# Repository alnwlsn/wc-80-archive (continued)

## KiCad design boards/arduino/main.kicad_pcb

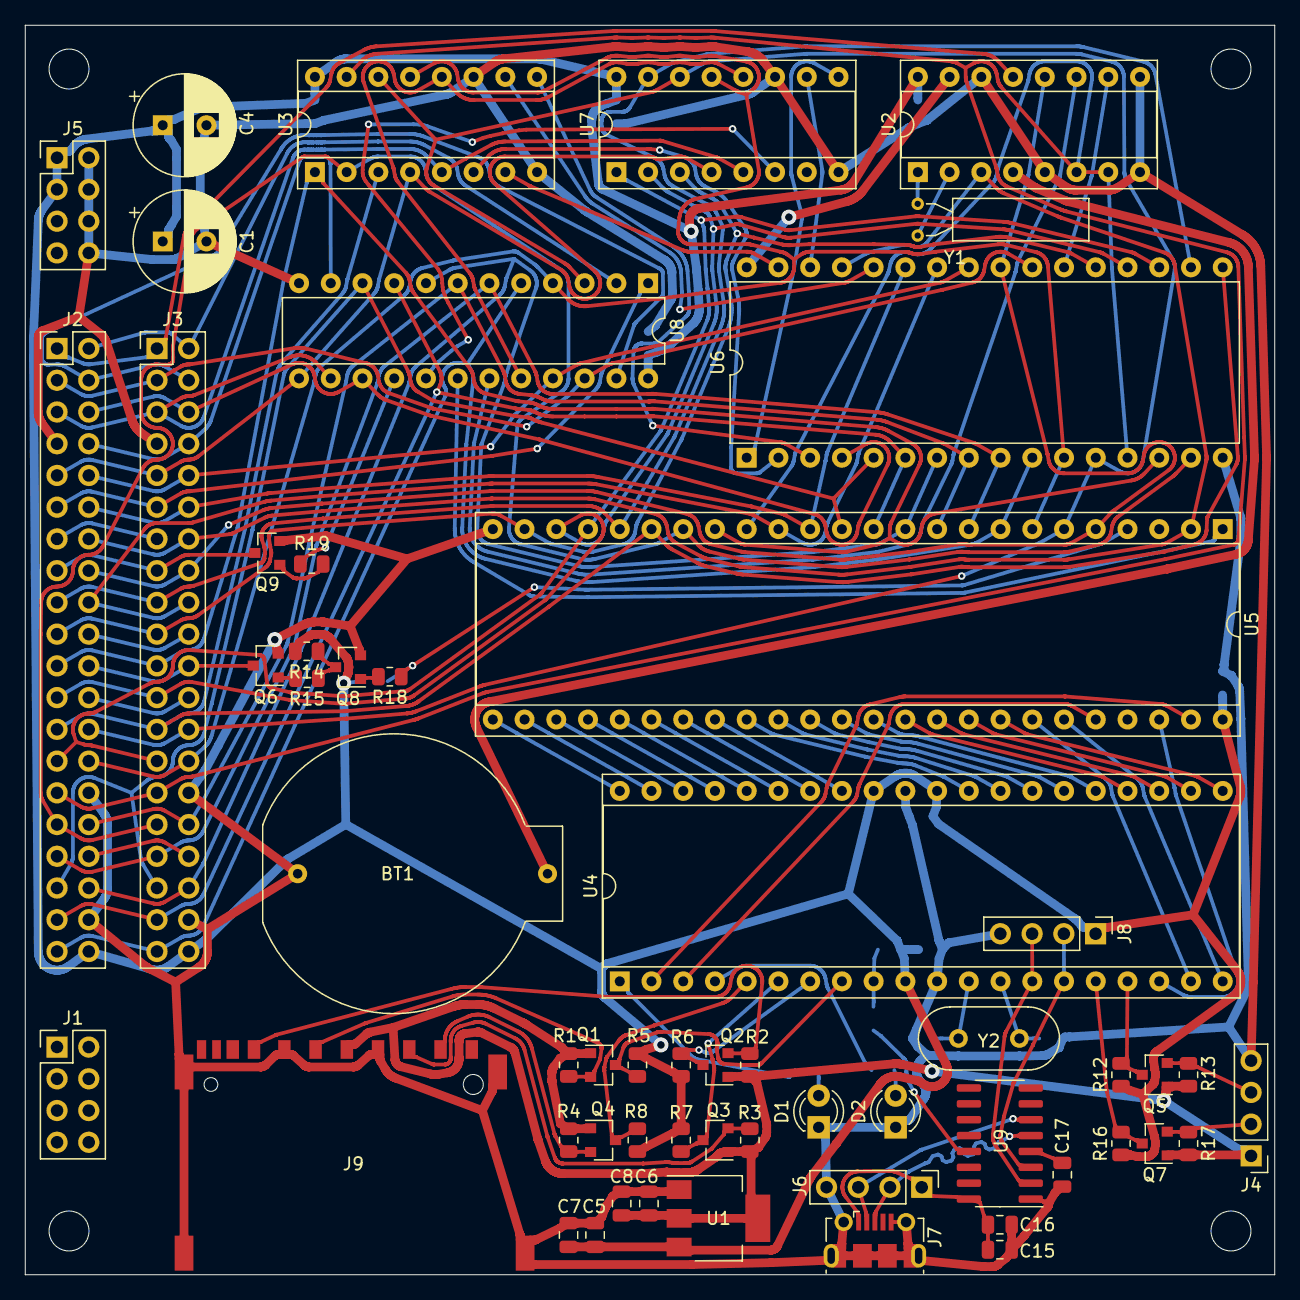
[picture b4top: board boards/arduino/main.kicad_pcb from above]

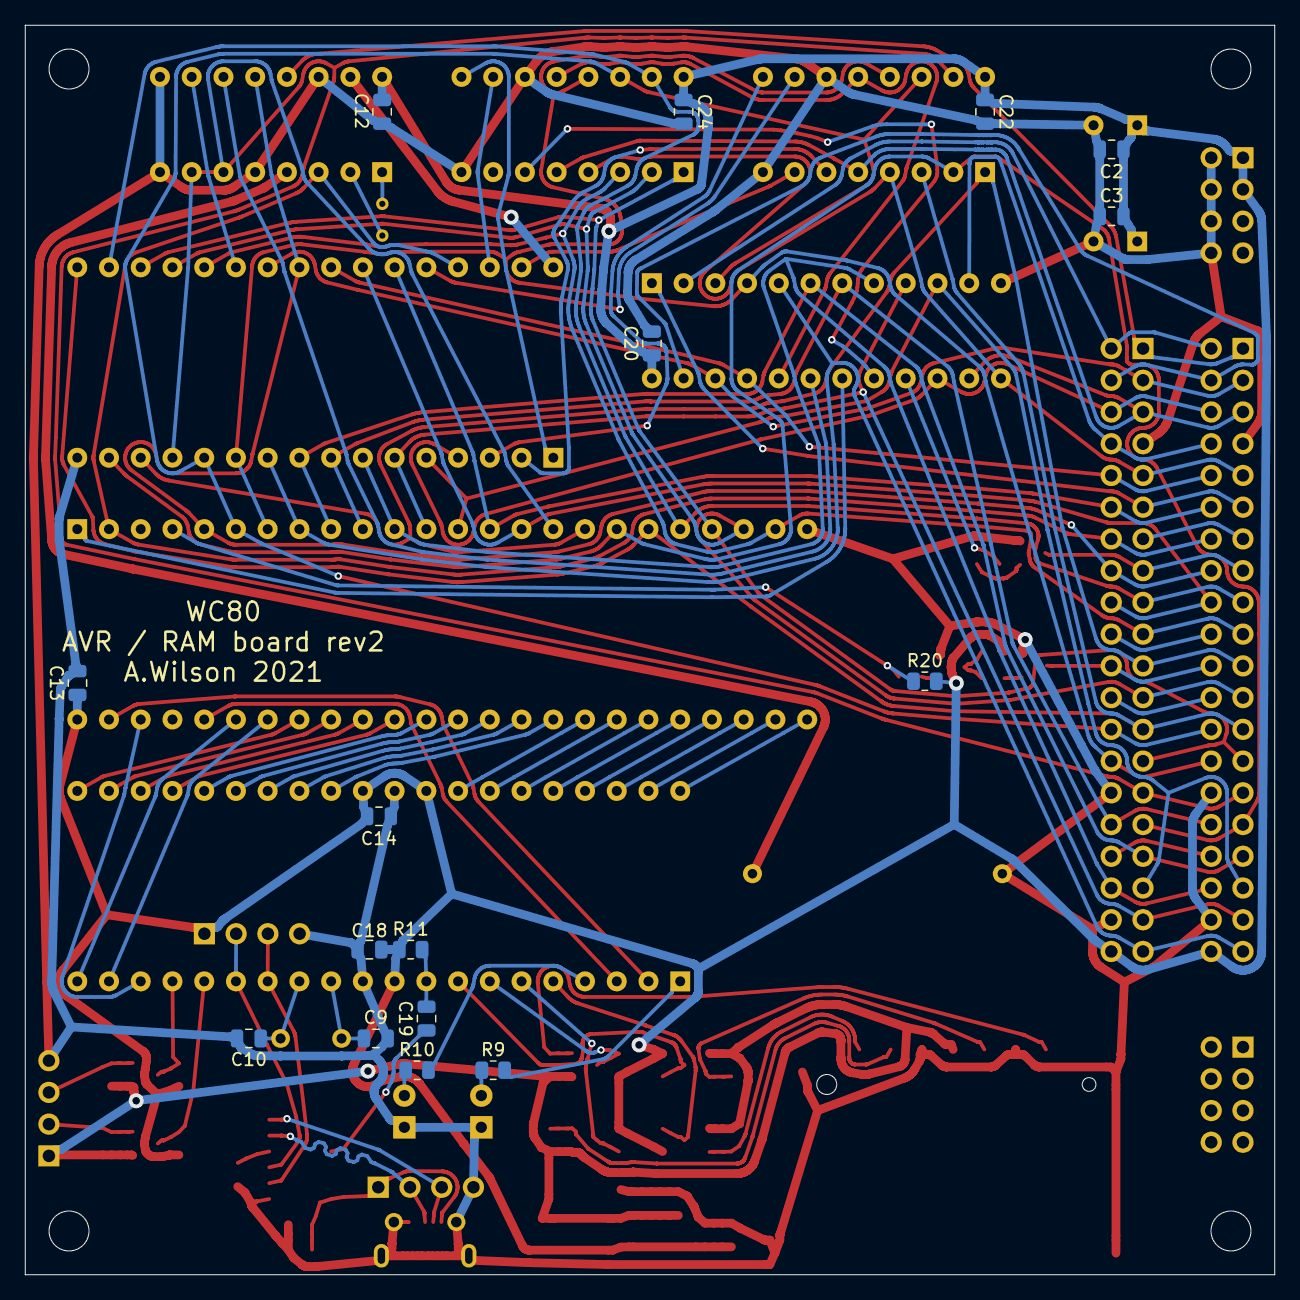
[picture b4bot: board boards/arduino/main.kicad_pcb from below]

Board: 2 copper layers, 100.0 x 100.0 mm, 77 parts (16 on the bottom side), 108 nets.

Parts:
BT1: Battery_Cell; BS-01-A4CJ004
C1, C4: 470uF; CP_Radial_D8.0mm_P3.50mm
C2, C3, C7, C8, C12, C13, C14, C18, C20, C22, C24: 100n; C_0805_2012Metric
C5, C6, C16: 10uF; C_0805_2012Metric
C9, C10: 22pF; C_0805_2012Metric
C15, C17, C19: 0.1uF; C_0805_2012Metric
D1: LED; LED_D3.0mm
D2: LED2; LED_D3.0mm
J1, J5: Conn_02x04_Odd_Even; PinHeader_2x04_P2.54mm_Vertical
J2, J3: TRS80W-header; PinHeader_2x20_P2.54mm_Vertical
J4, J6, J8: Conn_01x04_Male; PinHeader_1x04_P2.54mm_Vertical
J7: USB_B_Micro; USB_Micro-B_Molex-105017-0001
J9: SD_Card; SD_Card_ XUNPU_SD-101
M1, M2, M3, M4: 3mm-mounting-hole; MountingHole_3.2mm_M3_DIN965
Q1, Q2, Q3, Q4, Q5, Q6, Q7, Q8, Q9: BSS138; SOT-23
R1, R2, R3, R4, R5, R6, R7, R8, R11, R12, R13, R16, R17, R20: 10k; R_0805_2012Metric
R9, R10: 1000; R_0805_2012Metric
R14: 10000; R_0805_2012Metric
R15, R18, R19: 100; R_0805_2012Metric
U1: AMS1117-3.3; SOT-223-3_TabPin2
U2: DS1315; DIP-16_W7.62mm_Socket
U3, U7: 74HC670; DIP-16_W7.62mm_Socket
U4: mightycore-atmega1284p; DIP-40_W15.24mm_Socket
U5: IDT7130; DIP-48_W15.24mm_Socket
U6: AS6C4008; DIP-32_W15.24mm
U8: ATF22V10C; DIP-24_W7.62mm
U9: CH340C; SOIC-16_3.9x9.9mm_P1.27mm
Y1: 32768; Crystal_AT310_D3.0mm_L10.0mm_Horizontal
Y2: 16M; Crystal_HC49-U_Vertical

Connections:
+3V3: C6.2, C8.2, J4.1, J9.4, Q1.1, Q2.1, Q3.1, Q4.1, Q5.1, Q7.1, R1.1, R2.1, R3.1, R4.1, R13.1, R17.1, U1.2
+5V: C1.1, C2.1, C3.1, C4.1, C5.1, C7.1, C12.1, C13.1, C14.1, C18.1, C20.1, C22.1, C24.1, J2.40, J3.40, J5.1, J5.3, J8.1, R5.1, R6.1, R7.1, R8.1, R11.1, R12.1, R14.2, R16.1, R20.2, U1.3, U2.16, U3.16, U4.10, U4.30, U4.32, U5.48, U7.16, U8.24
AA0: U4.19, U5.42
AA1: U4.21, U5.41
AA2: U4.22, U5.40
AA3: U4.23, U5.39
AA4: U4.24, U5.38
AA5: U4.25, U5.37
AA6: U4.26, U5.36
AA7: U4.27, U5.35
AA8: U4.28, U5.34
AA9: U4.29, U5.33
AD0: U4.40, U5.25
AD1: U4.39, U5.26
AD2: U4.38, U5.27
AD3: U4.37, U5.28
AD4: U4.36, U5.29
AD5: U4.35, U5.30
AD6: U4.34, U5.31
AD7: U4.33, U5.32
CLK: J2.24, J3.24
F_A0: J2.26, J3.26, U3.14, U5.6, U6.12, U7.14, U8.3
F_A1: J2.28, J3.28, U3.13, U5.7, U6.11, U7.13, U8.4
F_A2: J2.39, J3.39, U5.8, U6.10, U8.5
F_A3: J2.33, J3.33, U5.9, U6.9, U8.6
F_A4: J2.32, J3.32, U5.10, U6.8, U8.7
F_A5: J2.36, J3.36, U5.11, U6.7, U8.8
F_A6: J2.37, J3.37, U5.12, U6.6, U8.9
F_A7: J2.35, J3.35, U5.13, U6.5, U8.10
F_A8: J2.12, J3.12, U5.14, U6.27
F_A9: J2.18, J3.18, U5.15, U6.26
F_A10: J2.3, J3.3, U6.23, U8.22
F_A11: J2.10, J3.10, U6.25, U8.21
F_A12: J2.6, J3.6, U6.4, U8.15
F_A13: J2.5, J3.5, U3.5, U7.5, U8.14
F_A14: J2.9, J3.9, U3.4, U7.4, U8.13
F_A15: J2.8, J3.8, U8.11
F_D0: J2.29, J3.29, U2.6, U2.7, U3.15, U5.16, U6.13
F_D1: J2.21, J3.21, U3.1, U5.17, U6.14
F_D2: J2.31, J3.31, U3.2, U5.18, U6.15
F_D3: J2.25, J3.25, U3.3, U5.19, U6.17
F_D4: J2.17, J3.17, U5.20, U6.18, U7.15
F_D5: J2.27, J3.27, U5.21, U6.19, U7.1
F_D6: J2.23, J3.23, U5.22, U6.20, U7.2
F_D7: J2.19, J3.19, U5.23, U6.21, U7.3
GND: BT1.2, C1.2, C2.2, C3.2, C4.2, C5.2, C6.1, C7.2, C8.1, C9.2, C10.2, C12.2, C13.2, C14.2, C15.2, C16.2, C17.2, C18.2, C20.2, C22.2, C24.2, D1.1, D2.1, J2.7, J2.30, J2.38, J3.7, J3.30, J3.38, J4.4, J5.2, J5.4, J5.6, J5.8, J6.4, J7.5, J7.6, J8.4, J9.3, J9.6, J9.12, J9.13, Q6.2, Q8.2, Q9.2, U1.1, U2.5, U2.8, U2.9, U2.14, U3.8, U3.11, U4.11, U4.31, U5.24, U6.16, U7.8, U7.11, U8.12, U9.1
unnamed: BT1.1, U2.4
unnamed: C9.1, U4.12, Y2.2
unnamed: C10.1, U4.13, Y2.1
unnamed: C15.1, C16.1, J6.1, J7.1, U9.16
unnamed: C17.1, U9.4
unnamed: C19.1, U9.13
unnamed: C19.2, R11.2, U4.9
unnamed: D1.2, R9.1
unnamed: D2.2, R10.1
unnamed: J4.2, Q7.2, R17.2
unnamed: J4.3, Q5.2, R13.2
unnamed: J6.2, J7.3, U9.5
unnamed: J6.3, J7.2, U9.6
unnamed: J8.2, U4.15, U9.3
unnamed: J8.3, U4.14, U9.2
unnamed: J9.1, Q4.2, R4.2
unnamed: J9.2, Q3.2, R3.2
unnamed: J9.5, Q1.2, R1.2
unnamed: J9.7, Q2.2, R2.2
unnamed: Q1.3, R5.2, U4.8
unnamed: Q2.3, R6.2, U4.7
unnamed: Q3.3, R7.2, U4.6
unnamed: Q4.3, R8.2, U4.5
unnamed: Q5.3, R12.2, U4.17
unnamed: Q6.1, R15.2
unnamed: Q7.3, R16.2, U4.16
unnamed: Q8.1, R18.2
unnamed: Q8.3, R14.1, R15.1
unnamed: Q9.1, R19.2
unnamed: R9.2, U4.1
unnamed: R10.2, U4.4
unnamed: R18.1, R20.1, U5.4
unnamed: R19.1, U8.16
unnamed: U2.1, Y1.2
unnamed: U2.2, Y1.1
unnamed: U2.10, U6.22
unnamed: U2.11, U8.19
unnamed: U2.15, U6.32
unnamed: U3.12, U7.12, U8.20
unnamed: U4.2, U5.47
unnamed: U4.3, U5.44
unnamed: U4.18, U5.46
unnamed: U4.20, U5.43
unnamed: U5.1, U8.18
S0: U3.10, U6.28
S1: U3.9, U6.3
S2: U3.7, U6.31
S3: U3.6, U6.2
S4: U6.30, U7.10
S5: U6.1, U7.9
~EN_EXTRA: U7.6, U8.17
~F_EXMEM~: J2.4, J3.4, U8.23
~F_INTAK~: J2.13, J3.13
~F_INT~: J2.22, J3.22, Q6.3
~F_INUSE~: J2.15, J3.15, Q9.3
~F_IN~: J2.20, J3.20
~F_MREQ~: J2.2, J3.2, U8.2
~F_OUT~: J2.11, J3.11, U8.1
~F_READ~: J2.16, J3.16, U2.12, U5.5, U6.24
~F_SYSRES~: J2.1, J3.1, U2.13
~F_WAIT~: J2.34, J3.34
~F_WRITE~: J2.14, J3.14, U2.3, U5.2, U6.29

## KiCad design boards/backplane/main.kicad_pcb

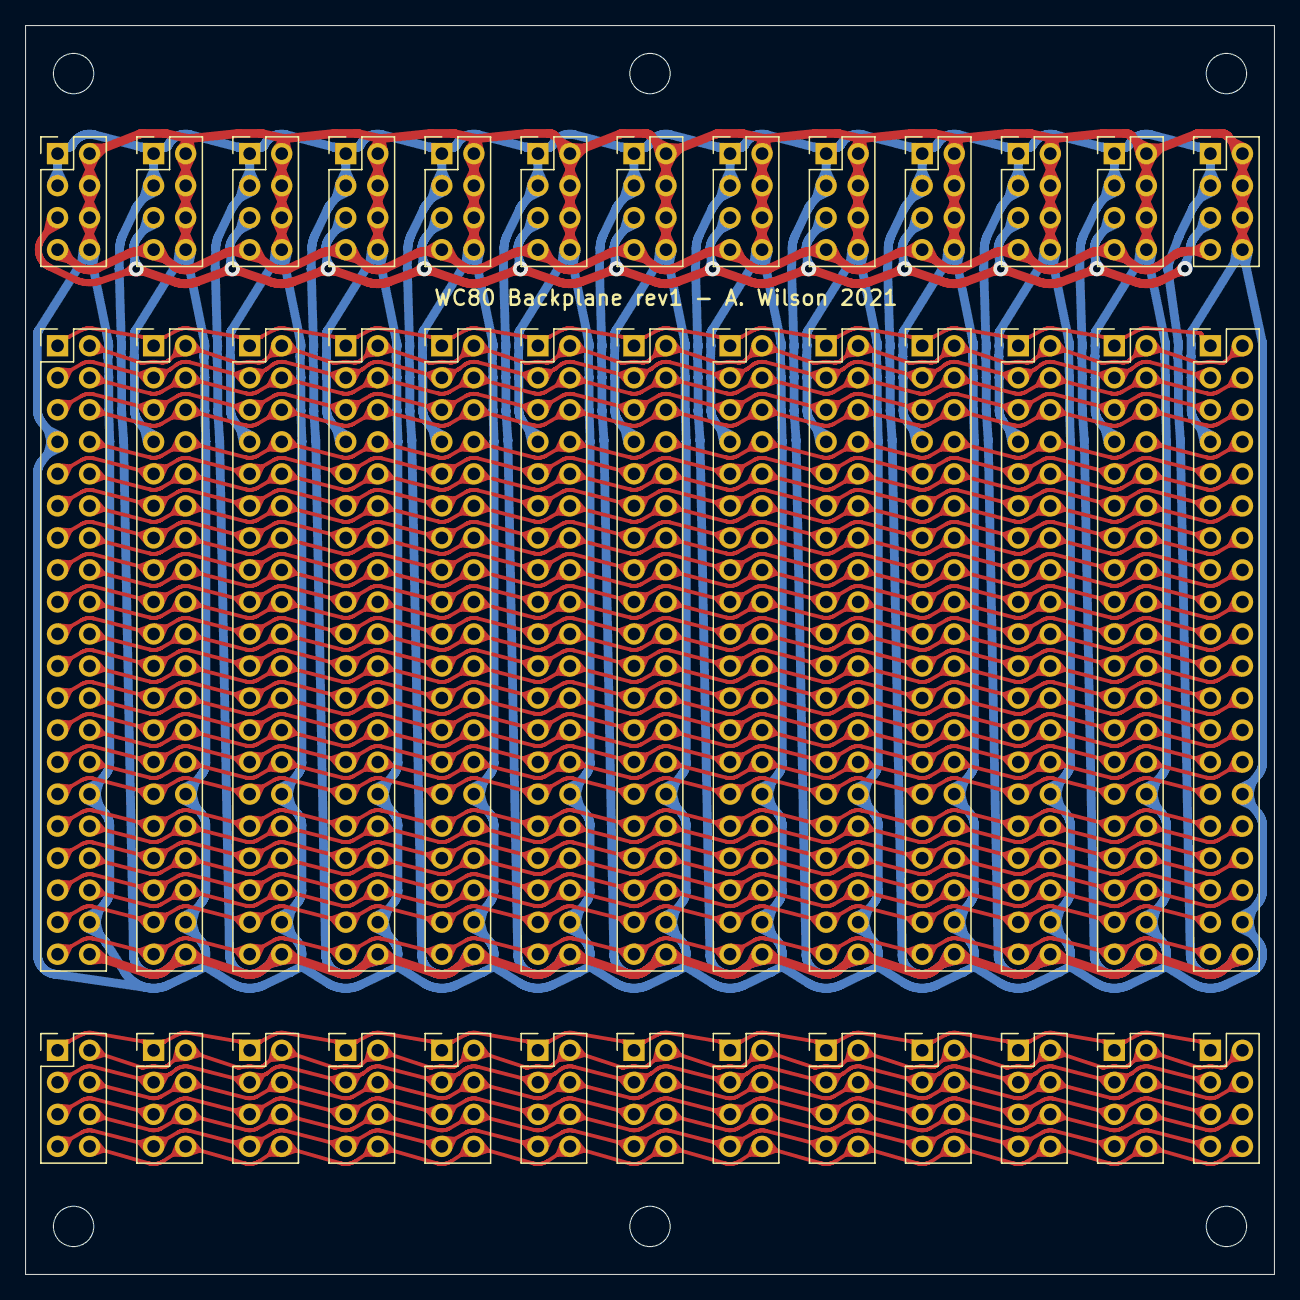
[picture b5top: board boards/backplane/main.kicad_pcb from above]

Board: 2 copper layers, 99.1 x 99.1 mm, 45 parts (0 on the bottom side), 48 nets.

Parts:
H1, H2, H3, H4, H5, H6: MountingHole; MountingHole_3.2mm_M3_DIN965
J1, J2, J4, J5, J6, J7, J8, J14, J15, J16, J17, J18, J19, J20, J21, J22, J23, J24, J31, J32, J33, J34, J35, J36, J37, J39: Conn_02x04_Odd_Even; PinHeader_2x04_P2.54mm_Vertical
J3, J9, J10, J11, J12, J13, J25, J26, J27, J28, J29, J30, J38: TRS80W-header; PinHeader_2x20_P2.54mm_Vertical

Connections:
+5V: J2.1, J2.3, J3.40, J4.1, J4.3, J5.1, J5.3, J6.1, J6.3, J7.1, J7.3, J8.1, J8.3, J9.40, J10.40, J11.40, J12.40, J13.40, J19.1, J19.3, J20.1, J20.3, J21.1, J21.3, J22.1, J22.3, J23.1, J23.3, J24.1, J24.3, J25.40, J26.40, J27.40, J28.40, J29.40, J30.40, J37.1, J37.3, J38.40
+12: J2.7, J4.7, J5.7, J6.7, J7.7, J8.7, J19.7, J20.7, J21.7, J22.7, J23.7, J24.7, J37.7
-5: J2.5, J4.5, J5.5, J6.5, J7.5, J8.5, J19.5, J20.5, J21.5, J22.5, J23.5, J24.5, J37.5
C1: J1.1, J14.1, J15.1, J16.1, J17.1, J18.1, J31.1, J32.1, J33.1, J34.1, J35.1, J36.1, J39.1
C2: J1.2, J14.2, J15.2, J16.2, J17.2, J18.2, J31.2, J32.2, J33.2, J34.2, J35.2, J36.2, J39.2
C3: J1.3, J14.3, J15.3, J16.3, J17.3, J18.3, J31.3, J32.3, J33.3, J34.3, J35.3, J36.3, J39.3
C4: J1.4, J14.4, J15.4, J16.4, J17.4, J18.4, J31.4, J32.4, J33.4, J34.4, J35.4, J36.4, J39.4
C5: J1.5, J14.5, J15.5, J16.5, J17.5, J18.5, J31.5, J32.5, J33.5, J34.5, J35.5, J36.5, J39.5
C6: J1.6, J14.6, J15.6, J16.6, J17.6, J18.6, J31.6, J32.6, J33.6, J34.6, J35.6, J36.6, J39.6
C7: J1.7, J14.7, J15.7, J16.7, J17.7, J18.7, J31.7, J32.7, J33.7, J34.7, J35.7, J36.7, J39.7
C8: J1.8, J14.8, J15.8, J16.8, J17.8, J18.8, J31.8, J32.8, J33.8, J34.8, J35.8, J36.8, J39.8
CLK: J3.24, J9.24, J10.24, J11.24, J12.24, J13.24, J25.24, J26.24, J27.24, J28.24, J29.24, J30.24, J38.24
F_A0: J3.26, J9.26, J10.26, J11.26, J12.26, J13.26, J25.26, J26.26, J27.26, J28.26, J29.26, J30.26, J38.26
F_A1: J3.28, J9.28, J10.28, J11.28, J12.28, J13.28, J25.28, J26.28, J27.28, J28.28, J29.28, J30.28, J38.28
F_A2: J3.39, J9.39, J10.39, J11.39, J12.39, J13.39, J25.39, J26.39, J27.39, J28.39, J29.39, J30.39, J38.39
F_A3: J3.33, J9.33, J10.33, J11.33, J12.33, J13.33, J25.33, J26.33, J27.33, J28.33, J29.33, J30.33, J38.33
F_A4: J3.32, J9.32, J10.32, J11.32, J12.32, J13.32, J25.32, J26.32, J27.32, J28.32, J29.32, J30.32, J38.32
F_A5: J3.36, J9.36, J10.36, J11.36, J12.36, J13.36, J25.36, J26.36, J27.36, J28.36, J29.36, J30.36, J38.36
F_A6: J3.37, J9.37, J10.37, J11.37, J12.37, J13.37, J25.37, J26.37, J27.37, J28.37, J29.37, J30.37, J38.37
F_A7: J3.35, J9.35, J10.35, J11.35, J12.35, J13.35, J25.35, J26.35, J27.35, J28.35, J29.35, J30.35, J38.35
F_A8: J3.12, J9.12, J10.12, J11.12, J12.12, J13.12, J25.12, J26.12, J27.12, J28.12, J29.12, J30.12, J38.12
F_A9: J3.18, J9.18, J10.18, J11.18, J12.18, J13.18, J25.18, J26.18, J27.18, J28.18, J29.18, J30.18, J38.18
F_A10: J3.3, J9.3, J10.3, J11.3, J12.3, J13.3, J25.3, J26.3, J27.3, J28.3, J29.3, J30.3, J38.3
F_A11: J3.10, J9.10, J10.10, J11.10, J12.10, J13.10, J25.10, J26.10, J27.10, J28.10, J29.10, J30.10, J38.10
F_A12: J3.6, J9.6, J10.6, J11.6, J12.6, J13.6, J25.6, J26.6, J27.6, J28.6, J29.6, J30.6, J38.6
F_A13: J3.5, J9.5, J10.5, J11.5, J12.5, J13.5, J25.5, J26.5, J27.5, J28.5, J29.5, J30.5, J38.5
F_A14: J3.9, J9.9, J10.9, J11.9, J12.9, J13.9, J25.9, J26.9, J27.9, J28.9, J29.9, J30.9, J38.9
F_A15: J3.8, J9.8, J10.8, J11.8, J12.8, J13.8, J25.8, J26.8, J27.8, J28.8, J29.8, J30.8, J38.8
F_D0: J3.29, J9.29, J10.29, J11.29, J12.29, J13.29, J25.29, J26.29, J27.29, J28.29, J29.29, J30.29, J38.29
F_D1: J3.21, J9.21, J10.21, J11.21, J12.21, J13.21, J25.21, J26.21, J27.21, J28.21, J29.21, J30.21, J38.21
F_D2: J3.31, J9.31, J10.31, J11.31, J12.31, J13.31, J25.31, J26.31, J27.31, J28.31, J29.31, J30.31, J38.31
F_D3: J3.25, J9.25, J10.25, J11.25, J12.25, J13.25, J25.25, J26.25, J27.25, J28.25, J29.25, J30.25, J38.25
F_D4: J3.17, J9.17, J10.17, J11.17, J12.17, J13.17, J25.17, J26.17, J27.17, J28.17, J29.17, J30.17, J38.17
F_D5: J3.27, J9.27, J10.27, J11.27, J12.27, J13.27, J25.27, J26.27, J27.27, J28.27, J29.27, J30.27, J38.27
F_D6: J3.23, J9.23, J10.23, J11.23, J12.23, J13.23, J25.23, J26.23, J27.23, J28.23, J29.23, J30.23, J38.23
F_D7: J3.19, J9.19, J10.19, J11.19, J12.19, J13.19, J25.19, J26.19, J27.19, J28.19, J29.19, J30.19, J38.19
GND: J2.2, J2.4, J2.6, J2.8, J3.7, J3.30, J3.38, J4.2, J4.4, J4.6, J4.8, J5.2, J5.4, J5.6, J5.8, J6.2, J6.4, J6.6, J6.8, J7.2, J7.4, J7.6, J7.8, J8.2, J8.4, J8.6, J8.8, J9.7, J9.30, J9.38, J10.7, J10.30, J10.38, J11.7, J11.30, J11.38, J12.7, J12.30, J12.38, J13.7, J13.30, J13.38, J19.2, J19.4, J19.6, J19.8, J20.2, J20.4, J20.6, J20.8, J21.2, J21.4, J21.6, J21.8, J22.2, J22.4, J22.6, J22.8, J23.2, J23.4, J23.6, J23.8, J24.2, J24.4, J24.6, J24.8, J25.7, J25.30, J25.38, J26.7, J26.30, J26.38, J27.7, J27.30, J27.38, J28.7, J28.30, J28.38, J29.7, J29.30, J29.38, J30.7, J30.30, J30.38, J37.2, J37.4, J37.6, J37.8, J38.7, J38.30, J38.38
~F_EXMEM~: J3.4, J9.4, J10.4, J11.4, J12.4, J13.4, J25.4, J26.4, J27.4, J28.4, J29.4, J30.4, J38.4
~F_INTAK~: J3.13, J9.13, J10.13, J11.13, J12.13, J13.13, J25.13, J26.13, J27.13, J28.13, J29.13, J30.13, J38.13
~F_INT~: J3.22, J9.22, J10.22, J11.22, J12.22, J13.22, J25.22, J26.22, J27.22, J28.22, J29.22, J30.22, J38.22
~F_INUSE~: J3.15, J9.15, J10.15, J11.15, J12.15, J13.15, J25.15, J26.15, J27.15, J28.15, J29.15, J30.15, J38.15
~F_IN~: J3.20, J9.20, J10.20, J11.20, J12.20, J13.20, J25.20, J26.20, J27.20, J28.20, J29.20, J30.20, J38.20
~F_MREQ~: J3.2, J9.2, J10.2, J11.2, J12.2, J13.2, J25.2, J26.2, J27.2, J28.2, J29.2, J30.2, J38.2
~F_OUT~: J3.11, J9.11, J10.11, J11.11, J12.11, J13.11, J25.11, J26.11, J27.11, J28.11, J29.11, J30.11, J38.11
~F_READ~: J3.16, J9.16, J10.16, J11.16, J12.16, J13.16, J25.16, J26.16, J27.16, J28.16, J29.16, J30.16, J38.16
~F_SYSRES~: J3.1, J9.1, J10.1, J11.1, J12.1, J13.1, J25.1, J26.1, J27.1, J28.1, J29.1, J30.1, J38.1
~F_WAIT~: J3.34, J9.34, J10.34, J11.34, J12.34, J13.34, J25.34, J26.34, J27.34, J28.34, J29.34, J30.34, J38.34
~F_WRITE~: J3.14, J9.14, J10.14, J11.14, J12.14, J13.14, J25.14, J26.14, J27.14, J28.14, J29.14, J30.14, J38.14

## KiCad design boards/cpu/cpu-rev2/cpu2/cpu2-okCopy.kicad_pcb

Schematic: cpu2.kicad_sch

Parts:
BT1: Battery_Cell; BS-01-A4CJ004
C1: 4u7; C_0805_2012Metric
C2: 2u2; C_0805_2012Metric
C3, C4, C5, C6, C7, C8, C9, C10, C11, C12, C13, C14, C15, C16, C18, C19, C20, C27, C28, C29: 100n; C_0805_2012Metric
C17, C21: 470uF; CP_Radial_D8.0mm_P3.50mm
C22: 100uF; CP_Elec_5x5.4
C23, C24: 220pF; C_0805_2012Metric
C25, C26: 10uF; C_0805_2012Metric
D3: HALT; LED_D3.0mm_FlatTop
D5: PWR; LED_D3.0mm_FlatTop
D8: 32; LED_D3.0mm_FlatTop
D9, D10, D11, D12, D13: 1N4148; D_SOD-123
J1, J2: Conn_02x04_Odd_Even; PinHeader_2x04_P2.54mm_Vertical
J3: TRS80W-header; PinHeader_2x20_P2.54mm_Vertical
J4: Conn_01x06_Male; PinHeader_1x06_P2.54mm_Vertical
M1, M2, M3, M4: 3mm-mounting-hole; MountingHole_3.2mm_M3_DIN965
Q1: 2N3904; TO-92_Inline
R3, R4, R52: 10; R_0805_2012Metric
R5, R6, R7, R9, R10, R15, R16, R17, R18, R19, R20, R21, R22, R23, R24, R25, R26, R27, R28, R29, R30, R31, R32, R33, R34, R35, R36, R37, R38, R39, R40, R41, R42, R43, R44, R45: 4k7; R_0805_2012Metric
R8, R11, R46, R48: 1K; R_0805_2012Metric
R47, R49: 7k5; R_0805_2012Metric
R50: 220K; R_0805_2012Metric
R51: 1.2K; R_0805_2012Metric
R53: 100; R_0805_2012Metric
R54, R61, R63, R65, R66: 470K; R_0805_2012Metric
R55, R59: 360K; R_0805_2012Metric
R56, R57: 1M; R_0805_2012Metric
R58: 560K; R_0805_2012Metric
R60: 1.8M; R_0805_2012Metric
R62: 680K; R_0805_2012Metric
R64: 10K; R_0805_2012Metric
SW1: NMI; SW_PUSH_6mm
SW2: RESET; SW_PUSH_6mm
U1, U20: 74LS175; SOIC-16_3.9x9.9mm_P1.27mm
U2: 74LS132; SOIC-14_3.9x8.7mm_P1.27mm
U3: 74LS163; SOIC-16_3.9x9.9mm_P1.27mm
U4: 74LS74; SOIC-14_3.9x8.7mm_P1.27mm
U5: Z80CPU; DIP-40_W15.24mm_Socket
U6: 74LS32; SOIC-14_3.9x8.7mm_P1.27mm
U8: SST39SF040; DIP-32_W15.24mm_Socket
U9: ATF22V10C; DIP-24_W7.62mm_Socket
U10: 74HC245; SO-20_5.3x12.6mm_P1.27mm
U11: AS6C4008; DIP-32_W15.24mm_Socket
U12, U15, U16: 74HC244; SO-20_5.3x12.6mm_P1.27mm
U13, U14: 74HC670; SOIC-16_3.9x9.9mm_P1.27mm
U17: LM3900D; SOIC-14_3.9x8.7mm_P1.27mm
U18: 74HCT02; SOIC-14_3.9x8.7mm_P1.27mm
U19: 74LS125; SOIC-14_3.9x8.7mm_P1.27mm
U21: SIP-1A05
U22: DS1210; SOIC-8_3.9x4.9mm_P1.27mm
X1: SG-7050CAN; Oscillator_SMD_SeikoEpson_SG8002CA-4Pin_7.0x5.0mm

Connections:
+5V: C1.1, C2.1, C3.1, C4.1, C5.1, C6.1, C7.1, C8.1, C9.1, C10.1, C11.1, C12.1, C13.1, C14.1, C15.1, C16.1, C17.1, C18.1, C19.1, C20.1, C21.1, C27.1, C28.1, C29.1, D3.2 (A), D5.2 (A), D9.1 (K), J2.1, J2.3, J3.40 (+5V), R7.2, R9.2, R10.2, R16.2, R17.2, R18.2, R19.2, R20.2, R45.2, R50.1, R52.1, R64.1, SW1.1 (A), SW2.1 (A), U1.16 (VCC), U2.14 (VCC), U3.16 (VCC), U4.14 (VCC), U5.11 (VCC), U6.14 (VCC), U8.31 (~WE), U8.32 (VCC), U9.24 (VCC), U10.20 (VCC), U12.20 (VCC), U13.16 (VCC), U14.16 (VCC), U15.20 (VCC), U16.20 (VCC), U18.14 (VCC), U19.14 (VCC), U20.16 (VCC), U21.3 (COIL2), U22.8 (VCCI), X1.1 (~ST), X1.4 (VCC)
A0: U5.30 (A0), U8.12 (A0), U9.10, U11.12 (A0), U12.2 (1A0), U13.14 (Wa), U14.14 (Wa)
A1: U5.31 (A1), U8.11 (A1), U9.9, U11.11 (A1), U12.4 (1A1), U13.13 (Wb), U14.13 (Wb)
A2: U5.32 (A2), U8.10 (A2), U9.8, U11.10 (A2), U12.6 (1A2)
A3: U5.33 (A3), U8.9 (A3), U9.7, U11.9 (A3), U12.8 (1A3)
A4: U5.34 (A4), U8.8 (A4), U9.6, U11.8 (A4), U12.17 (2A0)
A5: U5.35 (A5), U8.7 (A5), U9.5, U11.7 (A5), U12.15 (2A1)
A6: U5.36 (A6), U8.6 (A6), U9.4, U11.6 (A6), U12.13 (2A2)
A7: U5.37 (A7), U8.5 (A7), U9.3, U11.5 (A7), U12.11 (2A3)
A8: U5.38 (A8), U8.27 (A8), U11.27 (A8), U15.2 (1A0)
A9: U5.39 (A9), U8.26 (A9), U11.26 (A9), U15.4 (1A1)
A10: U5.40 (A10), U8.23 (A10), U11.23 (A10), U15.6 (1A2)
A11: U5.1 (A11), U8.25 (A11), U11.25 (A11), U15.8 (1A3)
A12: U5.2 (A12), U8.4 (A12), U11.4 (A12), U15.17 (2A0)
A13: U5.3 (A13), U8.28 (A13), U11.28 (A13), U15.15 (2A1)
A14: U5.4 (A14), U13.5 (Ra), U14.5 (Ra), U15.13 (2A2)
A15: U5.5 (A15), U13.4 (Rb), U14.4 (Rb), U15.11 (2A3)
BB_CE: U11.22 (~CE), U22.6 (~CEO)
BB_VCC: U11.32 (VCC), U22.1 (VCCO)
BUSISO: J1.7, R15.2, U10.19 (CE), U12.1 (1OE), U12.19 (2OE), U15.1 (1OE), U15.19 (2OE), U16.1 (1OE), U16.19 (2OE)
C1INN: R58.2, U17.6 (1IN-)
C1INP: R59.1, R60.2, U17.1 (1IN+)
C1OUT: D13.2 (A), R55.2, R58.1, R61.1, U17.5 (1OUT)
C2INN: R61.2, R63.1, U17.3 (2IN-)
C2INP: R62.1, U17.2 (2IN+)
C2OUT: D10.2 (A), R63.2, U17.4 (2OUT)
C3INN: R54.2, R56.1, U17.8 (3IN-)
C3INP: R57.2, U17.13 (3IN+)
C3OUT: D11.2 (A), R56.2, R66.2, U17.9 (3OUT)
C4INN: R65.1, U17.11 (4IN-)
C4INP: R66.1, U17.12 (4IN+)
CASIND: U2.1, U17.10 (4OUT)
CASSAIN: C23.2, J4.1, R53.1
CASSAOUT: J4.3, R47.2, R49.1, R51.2
CASSIN: U9.20, U19.1
CASSOUT: U2.5, U9.19, U20.9 (Cp)
CASS_SW1: J4.6, U21.1 (SW1)
CASS_SW2: J4.5, U21.4 (SW2)
CLK: J3.24 (CLK), U4.5 (Q), U5.6 (~CLK)
CLKD0: U1.2 (Q0), U3.3 (D0)
CLKD1: U1.7 (Q1), U3.4 (D1)
CLKD2: U1.10 (Q2), U3.5 (D2)
CLKDIV: U1.9 (Cp), U9.21
D0: R29.1, U1.4 (D0), U5.14 (D0), U8.13 (D0), U10.2 (A0), U11.13 (D0), U13.15 (D1), U20.4 (D0)
D1: R30.1, U1.5 (D1), U5.15 (D1), U8.14 (D1), U10.3 (A1), U11.14 (D1), U13.1 (D2), U20.5 (D1)
D2: R31.1, U1.12 (D2), U5.12 (D2), U8.15 (D2), U10.4 (A2), U11.15 (D2), U13.2 (D3), U20.12 (D2)
D3: R32.1, U1.13 (D3), U5.8 (D3), U8.17 (D3), U10.5 (A3), U11.17 (D3), U13.3 (D4), U20.13 (D3)
D4: R33.1, U5.7 (D4), U8.18 (D4), U10.6 (A4), U11.18 (D4), U14.15 (D1)
D5: R34.1, U5.9 (D5), U8.19 (D5), U10.7 (A5), U11.19 (D5), U14.1 (D2)
D6: R35.1, U5.10 (D6), U8.20 (D6), U10.8 (A6), U11.20 (D6), U14.2 (D3)
D7: R36.1, U5.13 (D7), U8.21 (D7), U10.9 (A7), U11.21 (D7), U14.3 (D4), U19.3
F_A0: J3.26 (A0), U12.18 (1Y0)
F_A1: J3.28 (A1), U12.16 (1Y1)
F_A2: J3.39 (A2), U12.14 (1Y2)
F_A3: J3.33 (A3), U12.12 (1Y3)
F_A4: J3.32 (A4), U12.3 (2Y0)
F_A5: J3.36 (A5), U12.5 (2Y1)
F_A6: J3.37 (A6), U12.7 (2Y2)
F_A7: J3.35 (A7), U12.9 (2Y3)
F_A8: J3.12 (A8), U15.18 (1Y0)
F_A9: J3.18 (A9), U15.16 (1Y1)
F_A10: J3.3 (A10), U15.14 (1Y2)
F_A11: J3.10 (A11), U15.12 (1Y3)
F_A12: J3.6 (A12), U15.3 (2Y0)
F_A13: J3.5 (A13), U15.5 (2Y1)
F_A14: J3.9 (A14), U15.7 (2Y2)
F_A15: J3.8 (A15), U15.9 (2Y3)
F_D0: J3.29 (D0), R37.1, U10.18 (B0)
F_D1: J3.21 (D1), R38.1, U10.17 (B1)
F_D2: J3.31 (D2), R39.1, U10.16 (B2)
F_D3: J3.25 (D3), R40.1, U10.15 (B3)
F_D4: J3.17 (D4), R41.1, U10.14 (B4)
F_D5: J3.27 (D5), R42.1, U10.13 (B5)
F_D6: J3.23 (D6), R43.1, U10.12 (B6)
F_D7: J3.19 (D7), R44.1, U10.11 (B7)
GND: BT1.2 (-), C3.2, C4.2, C5.2, C6.2, C7.2, C8.2, C9.2, C10.2, C11.2, C12.2, C13.2, C14.2, C15.2, C16.2, C17.2, C18.2, C19.2, C20.2, C21.2, C22.2, C25.2, C26.2, C27.2, C28.2, C29.2, D8.1 (K), J2.2, J2.4, J2.6, J2.8, J3.7 (GND), J3.30 (GND), J3.38 (GND), J4.2, J4.4, Q1.1 (E), R5.2, R6.2, R11.1, R15.1, R21.2, R22.2, R23.2, R24.2, R25.2, R26.2, R27.2, R28.2, R29.2, R30.2, R31.2, R32.2, R33.2, R34.2, R35.2, R36.2, R37.2, R38.2, R39.2, R40.2, R41.2, R42.2, R43.2, R44.2, R51.1, R53.2, U1.8 (GND), U2.7 (GND), U3.6 (D3), U3.8 (GND), U4.7 (GND), U4.11 (C), U4.12 (D), U5.29 (GND), U6.7 (GND), U8.16 (GND), U9.12 (GND), U10.10 (GND), U11.16 (GND), U12.10 (GND), U13.8 (GND), U14.8 (GND), U15.10 (GND), U16.10 (GND), U17.7 (GND), U18.7 (GND), U18.8, U18.9, U19.4, U19.7 (GND), U19.10, U19.13, U20.8 (GND), U22.3 (TOL), U22.4 (GND), U22.7 (VBAT2), X1.2 (GND)
M1: U5.27 (~M1), U18.5
MEMCHIP: R26.1, U9.14, U14.9 (Q2)
unnamed: BT1.1 (+), U22.2 (VBAT1)
unnamed: C1.2, R3.1, R5.1, U2.9, U2.10
unnamed: C2.2, R4.1, R6.1, U2.12, U2.13
unnamed: C22.1, R52.2, U17.14 (VCC)
unnamed: C23.1, C24.1, R55.1
unnamed: C24.2, R59.2
unnamed: C25.1, R57.1, R60.1, R62.2, R64.2
unnamed: C26.1, D12.1 (K), R65.2
unnamed: D3.1 (K), R8.2
unnamed: D5.1 (K), R11.2
unnamed: D8.2 (A), R46.1
unnamed: D9.2 (A), Q1.3 (C), U21.2 (COIL1)
unnamed: D10.1 (K), D13.1 (K), R54.1
unnamed: D11.1 (K), D12.2 (A)
unnamed: J1.1, R4.2, SW2.2 (B)
unnamed: J1.3, R3.2, SW1.2 (B)
unnamed: J1.5, U2.8, U5.17 (~NMI)
unnamed: Q1.2 (B), R48.1
unnamed: R7.1, U3.1 (~MR), U3.7 (CEP), U3.10 (CET)
unnamed: R8.1, U5.18 (~HALT)
unnamed: R9.1, U5.25 (~BUSRQ)
unnamed: R10.1, U4.1 (~R), U4.4 (~S)
unnamed: R45.1, U20.1 (~Mr)
unnamed: R46.2, U20.15 (Q3)
unnamed: R47.1, U20.2 (Q0)
unnamed: R48.2, U20.10 (Q2)
unnamed: R49.2, R50.2, U20.6 (~Q1)
unnamed: U2.2, U2.6
unnamed: U3.2 (CP), X1.3 (OUT)
unnamed: U4.2 (D), U4.6 (~Q)
unnamed: U4.8 (~Q), U13.11 (~RD), U14.11 (~RD)
unnamed: U3.9 (~PE), U18.1
unnamed: U3.11 (Q3), U4.3 (C), U18.2, U18.3
unnamed: U18.4, U18.11, U18.12
unnamed: U2.3, U2.4, U19.2
RAM~ROM~: R27.1, U9.15
S0: R21.1, U8.29 (A14), U11.3 (A14), U13.10 (Q1)
S1: R22.1, U8.3 (A15), U11.31 (A15), U13.9 (Q2)
S2: R23.1, U8.2 (A16), U11.2 (A16), U13.7 (Q3)
S3: R24.1, U8.30 (A17), U11.30 (A17), U13.6 (Q4)
S4: R25.1, U8.1 (A18), U11.1 (A18), U14.10 (Q1)
~BUSBUF~: U9.22, U10.1 (A->B)
~BankSel~: U4.10 (~S), U9.16, U13.12 (~WR), U14.12 (~WR)
~EXMEM~: R28.1, U14.6 (Q4), U16.6 (1A2)
~F_EXMEM~: J3.4 (~EXMEM), U16.14 (1Y2)
~F_INTAK~: J3.13 (~INTAK), U16.12 (1Y3)
~F_INT~: J3.22 (~INT), R19.1, U19.5
~F_INUSE~: J3.15 (~INUSE), R18.1, U19.9
~F_IN~: J3.20 (~IN), U16.5 (2Y1)
~F_MREQ~: J3.2 (~RAS), U16.16 (1Y1)
~F_OUT~: J3.11 (~OUT), U16.3 (2Y0)
~F_READ~: J3.16 (~RD), U16.9 (2Y3)
~F_SYSRES~: J3.1 (~SYSRES), U16.18 (1Y0)
~F_WAIT~: J3.34 (~WAIT), R20.1, U19.12
~F_WRITE~: J3.14 (~WR), U16.7 (2Y2)
~INTAK~: U16.8 (1A3), U18.13
~INT~: R16.1, U5.16 (~INT), U19.6
~INUSE~: U9.13, U19.8
~IN~: U6.8, U16.15 (2A1)
~IORQ~: U5.20 (~IORQ), U6.10, U6.13, U9.23, U18.6
~MREQ~: U5.19 (~MREQ), U6.2, U6.5, U9.2, U16.4 (1A1)
~OUT~: U6.11, U9.1, U16.17 (2A0)
~RAM0~: U9.18, U22.5 (~CE)
~RD~: U5.21 (~RD), U6.1, U6.9, U9.11
~READ~: U6.3, U8.24 (~OE), U11.24 (~OE), U16.11 (2A3)
~ROM0~: U8.22 (~CE), U9.17
~SYSRES~: U1.1 (~Mr), U2.11, U4.13 (~R), U5.26 (~RESET), U16.2 (1A0)
~WAIT~: R17.1, U5.24 (~WAIT), U19.11
~WRITE~: U6.6, U11.29 (~WE), U16.13 (2A2)
~WR~: U5.22 (~WR), U6.4, U6.12

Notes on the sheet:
WC-80 CPU rev2 - Alan Wilson 2022
rev3 - ~OUT~ can be changed to ~WR~, because ~OUT~ can be derived

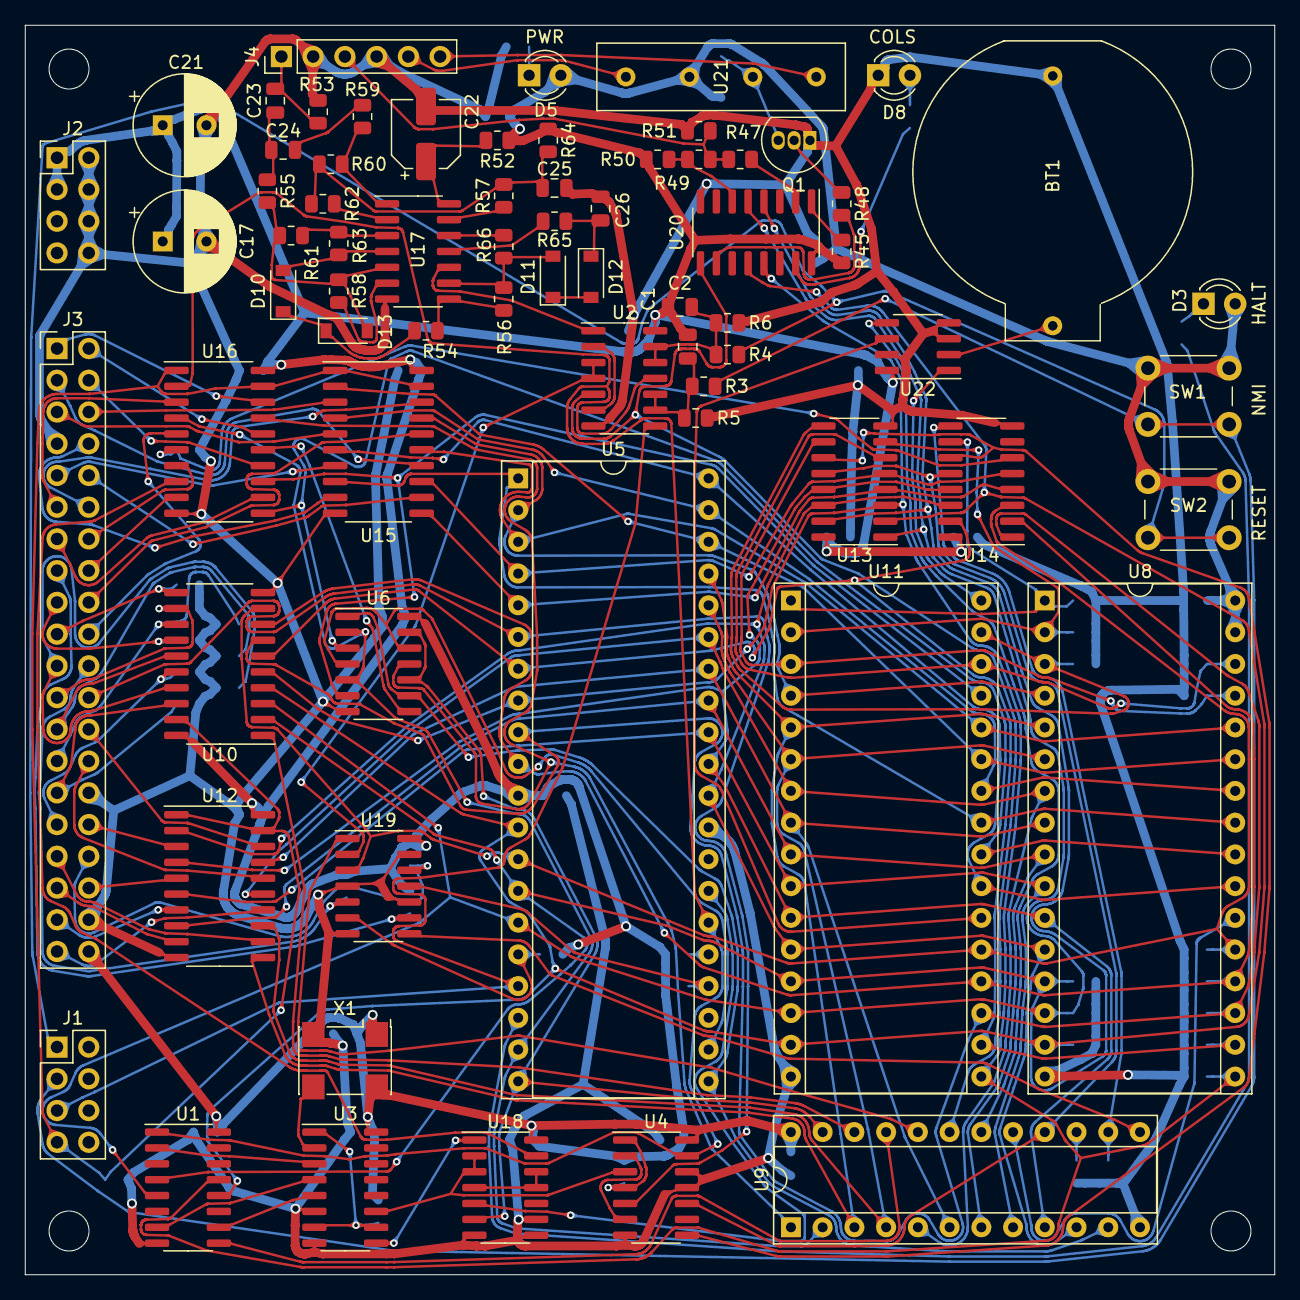
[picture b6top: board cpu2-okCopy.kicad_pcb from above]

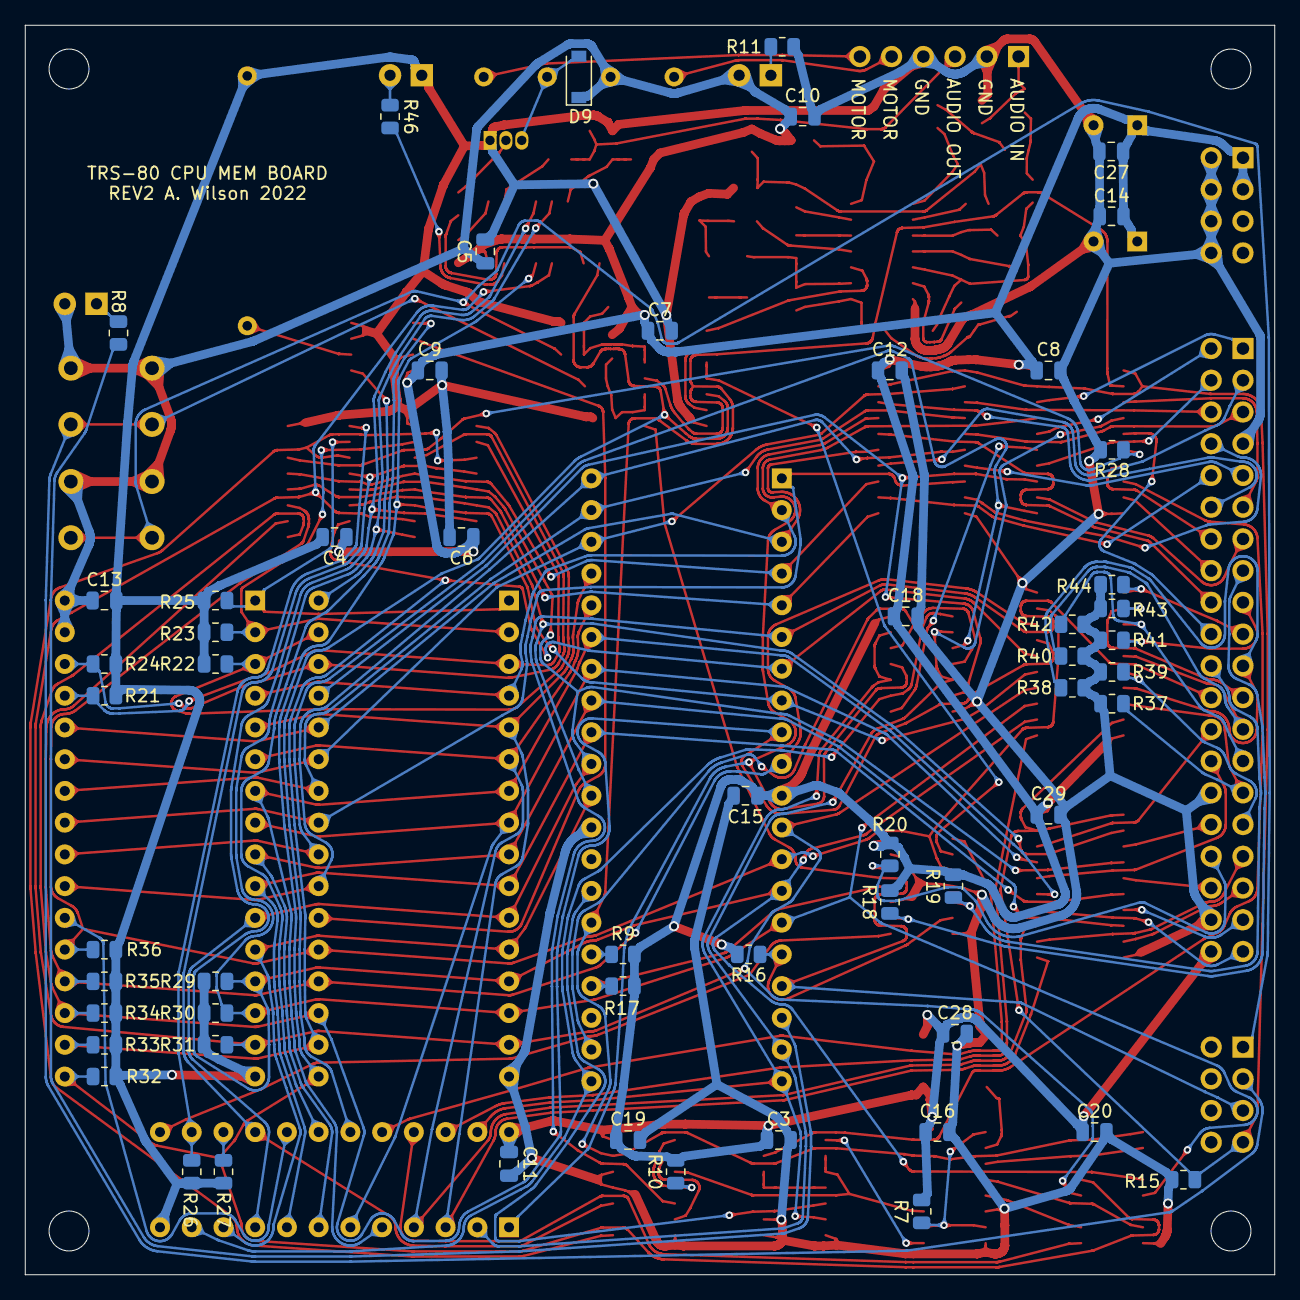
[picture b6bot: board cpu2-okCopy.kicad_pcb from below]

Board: 2 copper layers, 100.0 x 100.0 mm, 132 parts (57 on the bottom side), 148 nets.
